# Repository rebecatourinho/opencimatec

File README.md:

opencimatec
===========

Neste repositório encontram-se os arquivos referentes ao projeto open source hardware (OSH) do sistema embarcado voltado à instrumentação eletrônica proposto e desenvolvido pela engenheira eletricista Rebeca Tourinho do SENAI CIMATEC - Salvador, Brasil.

In this repository can be found all project files of the open source hardware (OSH) electronics instrumentation embedded system suggested and developed by Rebeca Tourinho, electrical engineer of SENAI CIMATEC - Salvador, Brazil.

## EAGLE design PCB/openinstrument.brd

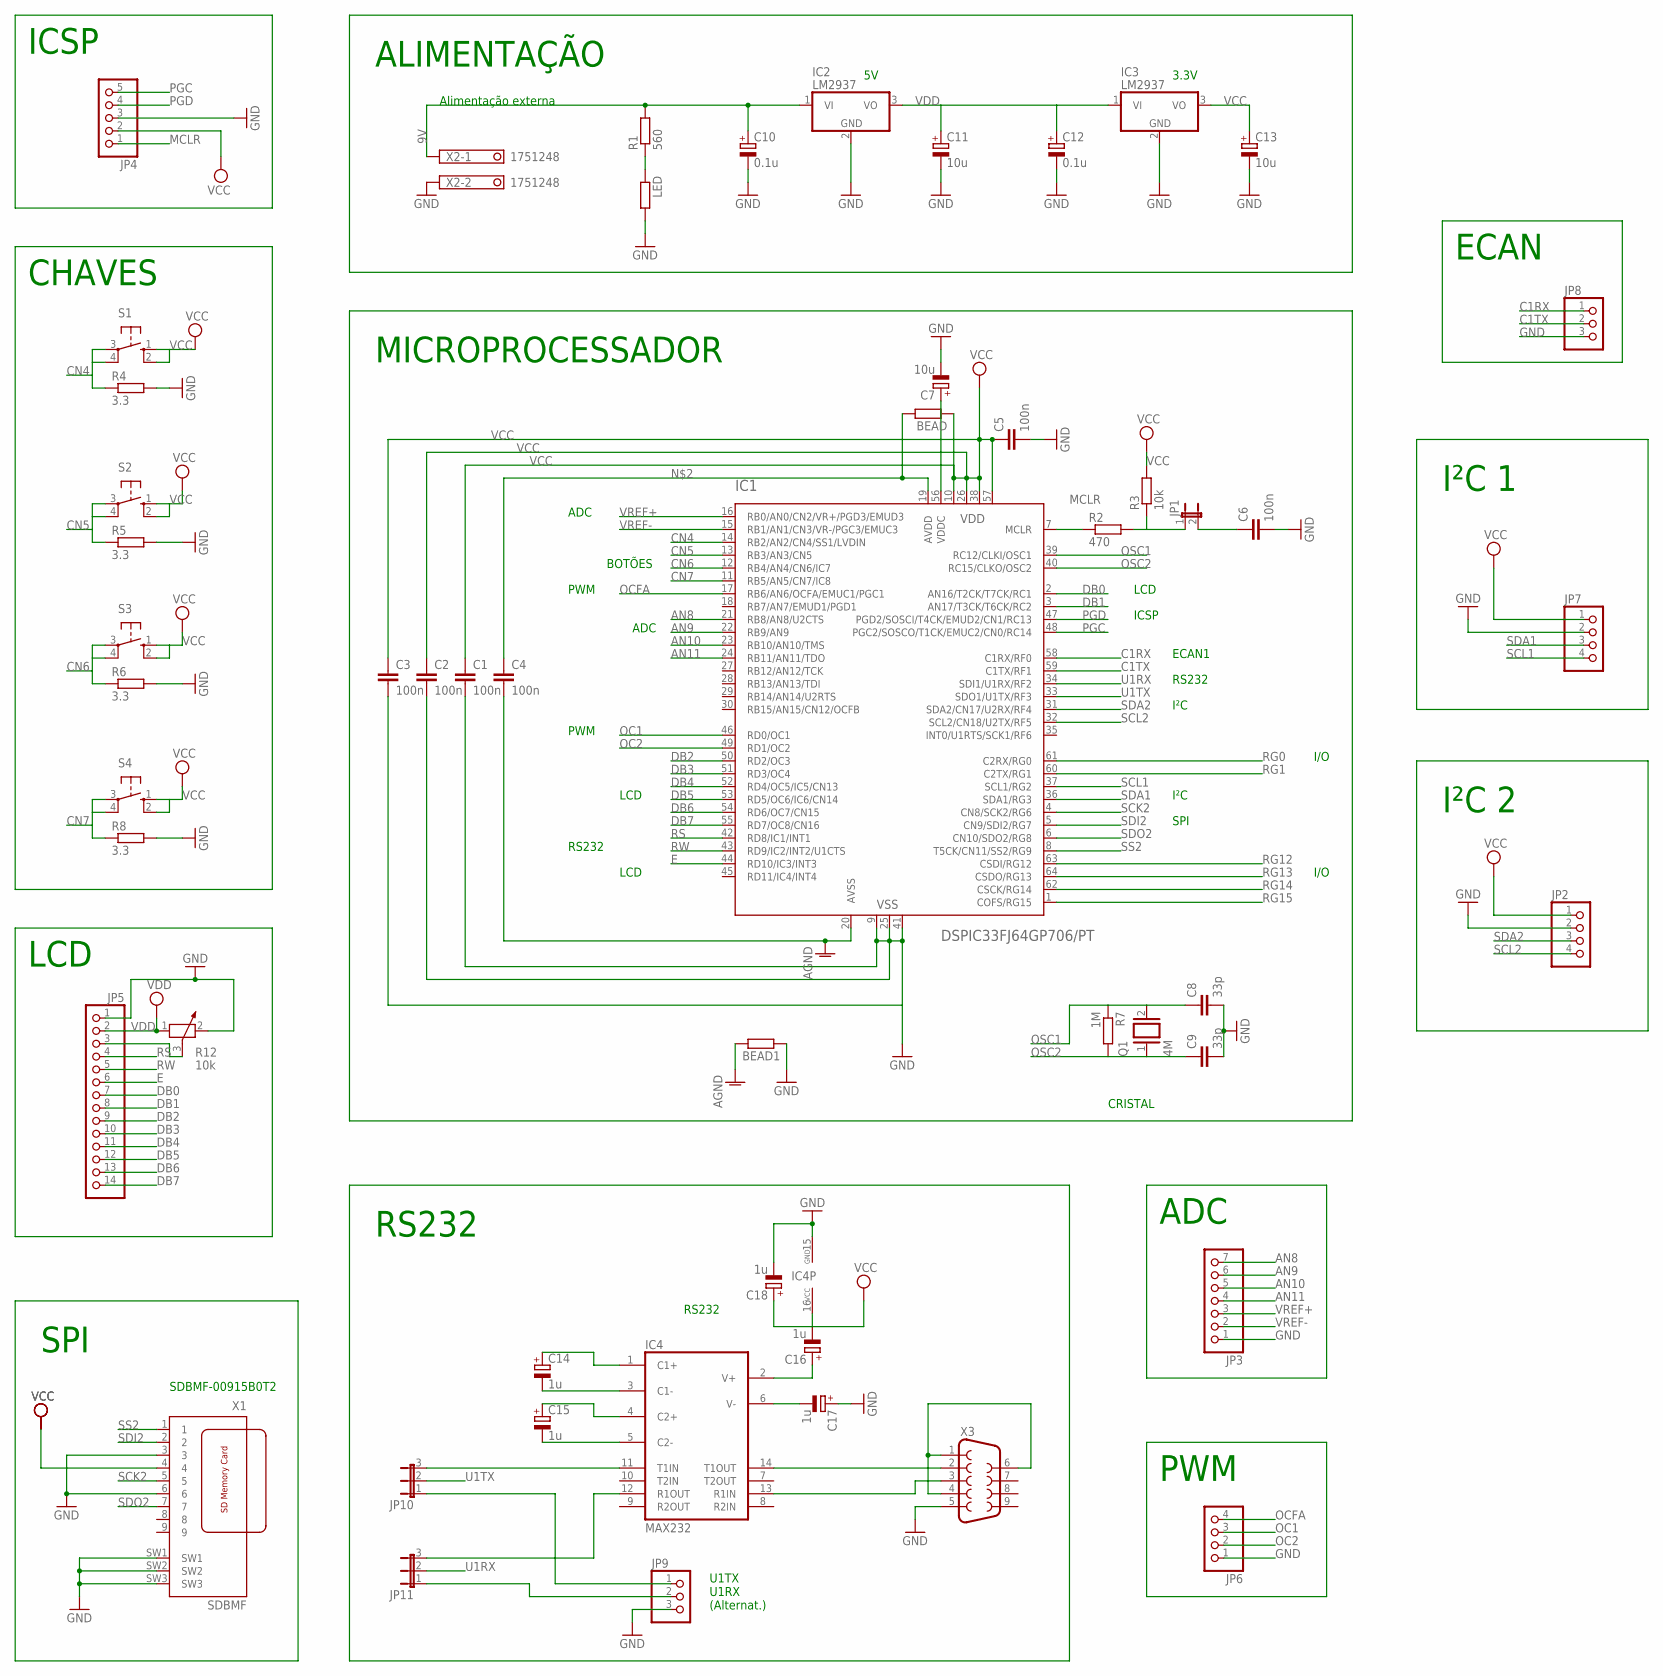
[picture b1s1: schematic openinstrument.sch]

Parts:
BEAD, BEAD1: R-EU_R0805; R0805
C1, C2, C3, C4, C5, C6: 100n; C0805
C7, C11, C13: 10u; E2,5-5
C8, C9: 33p; C0805
C10, C12: 0.1u; E2,5-5
C14, C15, C16, C17, C18: 1u; E2,5-5
IC1: DSPIC33FJ64GP706/PT; TQFP64-10X10
IC2, IC3: LM2937; TO263-3
IC4: MAX232; DIL16
JP1: JP1E; JP1
JP2, JP6, JP7: PINHD-1X4; 1X04
JP3: PINHD-1X7; 1X07
JP4: PINHD-1X5; 1X05
JP5: PINHD-1X14; 1X14
JP8, JP9: PINHD-1X3; 1X03
JP10, JP11: JP2E; JP2
LED: R-EU_R0805; R0805
Q1: 4M; QS
R1: 560; R0805
R2: 470; R0805
R3: 10k; R0805
R4, R5, R6, R8: 3.3; R0805
R7: 1M; R0805
R12: 10k; PT-10S
S1, S2, S3, S4: 10-XX; B3F-10XX
X1: SDBMF; SDBMF-009XXBXX2
X2: 1751248
X3: F09H

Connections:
9V: C10.+, IC2.1 (VI), R1.2, X2.1
AGND: BEAD1.2, C4.2, IC1.20 (AVSS)
AN8: IC1.21 (RB8/AN8/U2CTS), JP3.7
AN9: IC1.22 (RB9/AN9), JP3.6
AN10: IC1.23 (RB10/AN10/TMS), JP3.5
AN11: IC1.24 (RB11/AN11/TDO), JP3.4
C1RX: IC1.58 (C1RX/RF0), JP8.1
C1TX: IC1.59 (C1TX/RF1), JP8.2
CN4: IC1.14 (RB2/AN2/CN4/SS1/LVDIN), R4.1, S1.3, S1.4 (P1)
CN5: IC1.13 (RB3/AN3/CN5), R5.1, S2.3, S2.4 (P1)
CN6: IC1.12 (RB4/AN4/CN6/IC7), R6.1, S3.3, S3.4 (P1)
CN7: IC1.11 (RB5/AN5/CN7/IC8), R8.1, S4.3, S4.4 (P1)
DB0: IC1.2 (AN16/T2CK/T7CK/RC1), JP5.7
DB1: IC1.3 (AN17/T3CK/T6CK/RC2), JP5.8
DB2: IC1.50 (RD2/OC3), JP5.9
DB3: IC1.51 (RD3/OC4), JP5.10
DB4: IC1.52 (RD4/OC5/IC5/CN13), JP5.11
DB5: IC1.53 (RD5/OC6/IC6/CN14), JP5.12
DB6: IC1.54 (RD6/OC7/CN15), JP5.13
DB7: IC1.55 (RD7/OC8/CN16), JP5.14
E: IC1.44 (RD10/IC3/INT3), JP5.6
GND: BEAD1.1, C1.2, C2.2, C3.2, C5.2, C6.2, C7.-, C8.2, C9.2, C10.-, C11.-, C12.-, C13.-, C17.+, C18.-, IC1.9 (VSS), IC1.25 (VSS), IC1.41 (VSS), IC2.2 (GND), IC3.2 (GND), IC4.15 (GND), JP2.2, JP3.1, JP4.3, JP5.1, JP6.1, JP7.2, JP8.3, JP9.3, LED.2, R4.2, R5.2, R6.2, R8.2, R12.2, X1.3, X1.6, X1.SW1, X1.SW2, X1.SW3, X2.2, X3.5
MCLR: JP4.1, R2.1
unnamed: JP5.3, R12.3
unnamed: BEAD.2, C4.1, IC1.19 (AVDD)
unnamed: JP1.1, R2.2, R3.1
unnamed: C6.1, JP1.2
unnamed: IC4.14 (T1OUT), X3.2
unnamed: C14.-, IC4.3 (C1-)
unnamed: C14.+, IC4.1 (C1+)
unnamed: C15.-, IC4.5 (C2-)
unnamed: C7.+, IC1.56 (VDDC)
unnamed: LED.1, R1.1
unnamed: C15.+, IC4.4 (C2+)
unnamed: C16.+, IC4.2 (V+)
unnamed: C17.-, IC4.6 (V-)
unnamed: IC4.13 (R1IN), X3.3
unnamed: X3.1, X3.4, X3.6
unnamed: IC4.12 (R1OUT), JP11.3
unnamed: JP9.1, JP10.1
unnamed: IC4.11 (T1IN), JP10.3
unnamed: JP9.2, JP11.1
OC1: IC1.46 (RD0/OC1), JP6.3
OC2: IC1.49 (RD1/OC2), JP6.2
OCFA: IC1.17 (RB6/AN6/OCFA/EMUC1/PGC1), JP6.4
OSC1: C8.1, IC1.39 (RC12/CLKI/OSC1), Q1.2, R7.1
OSC2: C9.1, IC1.40 (RC15/CLKO/OSC2), Q1.1, R7.2
PGC: IC1.48 (PGC2/SOSCO/T1CK/EMUC2/CN0/RC14), JP4.5
PGD: IC1.47 (PGD2/SOSCI/T4CK/EMUD2/CN1/RC13), JP4.4
RG0: IC1.61 (C2RX/RG0)
RG1: IC1.60 (C2TX/RG1)
RG12: IC1.63 (CSDI/RG12)
RG13: IC1.64 (CSDO/RG13)
RG14: IC1.62 (CSCK/RG14)
RG15: IC1.1 (COFS/RG15)
RS: IC1.42 (RD8/IC1/INT1), JP5.4
RW: IC1.43 (RD9/IC2/INT2/U1CTS), JP5.5
SCK2: IC1.4 (CN8/SCK2/RG6), X1.5
SCL1: IC1.37 (SCL1/RG2), JP7.4
SCL2: IC1.32 (SCL2/CN18/U2TX/RF5), JP2.4
SDA1: IC1.36 (SDA1/RG3), JP7.3
SDA2: IC1.31 (SDA2/CN17/U2RX/RF4), JP2.3
SDI2: IC1.5 (CN9/SDI2/RG7), X1.2
SDO2: IC1.6 (CN10/SDO2/RG8), X1.7
SS2: IC1.8 (T5CK/CN11/SS2/RG9), X1.1
U1RX: IC1.34 (SDI1/U1RX/RF2), JP11.2
U1TX: IC1.33 (SDO1/U1TX/RF3), JP10.2
VCC: BEAD.1, C1.1, C2.1, C3.1, C5.1, C13.+, C16.-, C18.+, IC1.10 (VDD), IC1.26 (VDD), IC1.38 (VDD), IC1.57 (VDD), IC3.3 (VO), IC4.16 (VCC), JP2.1, JP4.2, JP7.1, R3.2, S1.1 (S), S1.2 (S1), S2.1 (S), S2.2 (S1), S3.1 (S), S3.2 (S1), S4.1 (S), S4.2 (S1), X1.4
VDD: C11.+, C12.+, IC2.3 (VO), IC3.1 (VI), JP5.2, R12.1
VREF+: IC1.16 (RB0/AN0/CN2/VR+/PGD3/EMUD3), JP3.3
VREF-: IC1.15 (RB1/AN1/CN3/VR-/PGC3/EMUC3), JP3.2

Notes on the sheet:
ICSP
LCD
SDBMF-00915B0T2
Alimentação externa
3.3V
ECAN1
RS232
I²C
SPI
PWM
ADC
BOTÕES
I/O
CRISTAL
CHAVES
ECAN
U1TX U1RX (Alternat.)
ALIMENTAÇÃO
MICROPROCESSADOR
I²C 1
I²C 2

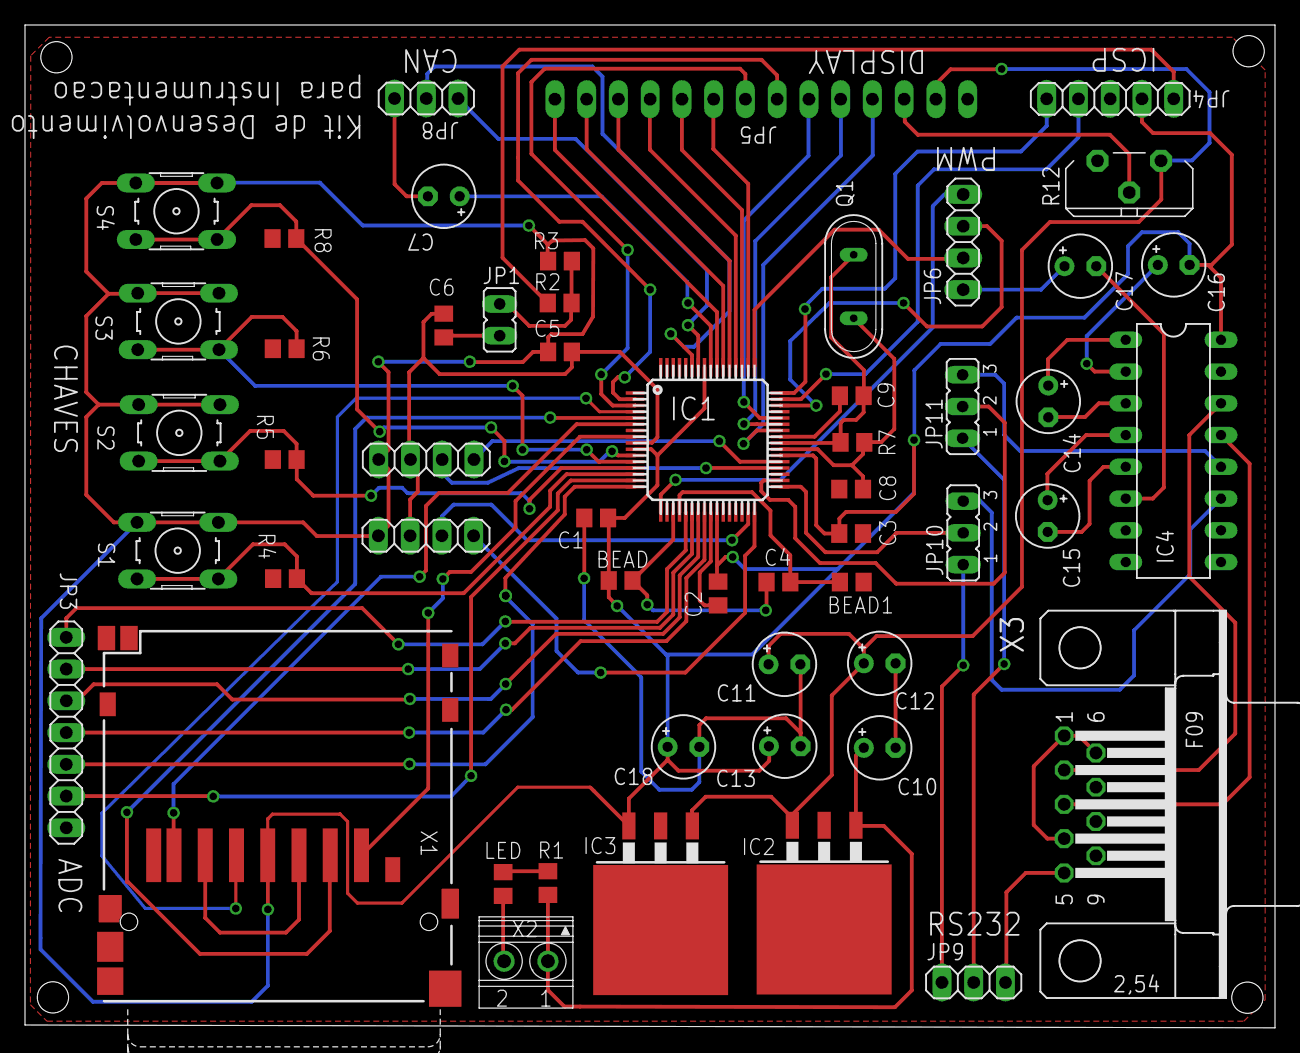
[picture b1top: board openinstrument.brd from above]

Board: 2 copper layers, 100.0 x 80.2 mm, 53 parts (1 on the bottom side), 65 nets.

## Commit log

2014-08-30 biblioteca dspic
2014-08-30 Arquivos PCI/PCB Files
2014-08-30 Firmware
